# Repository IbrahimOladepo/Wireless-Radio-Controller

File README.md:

# Wireless Radio Controller
 A wireless radio controller DIY project based on NRF24L01 and Arduino

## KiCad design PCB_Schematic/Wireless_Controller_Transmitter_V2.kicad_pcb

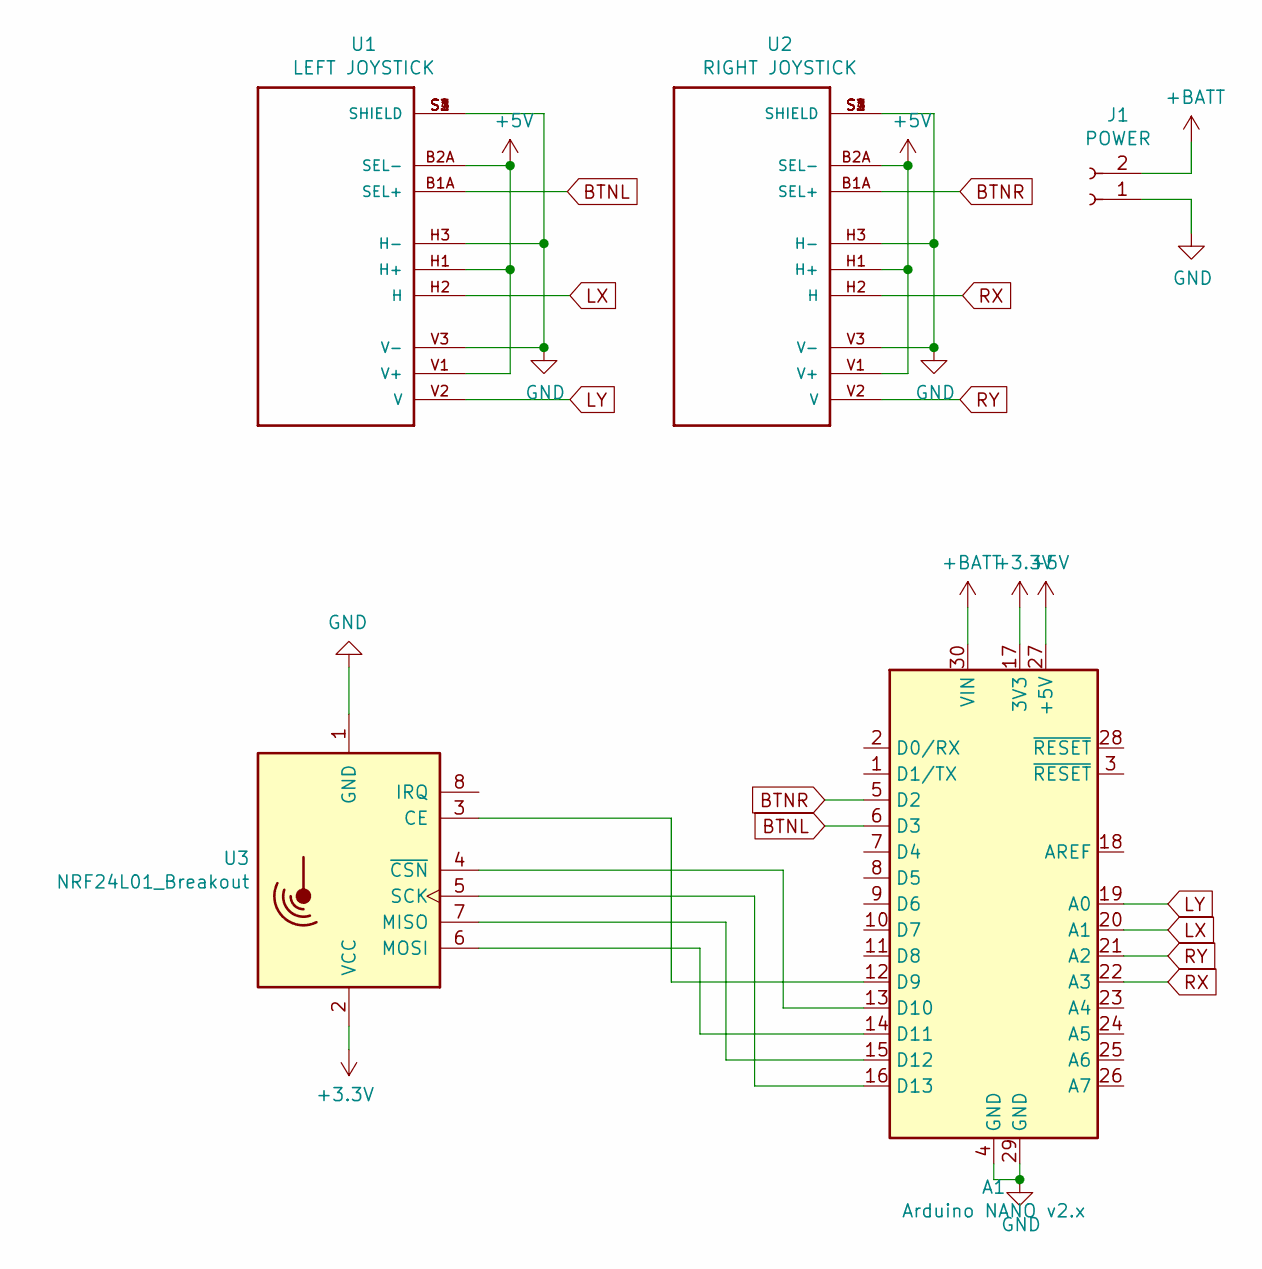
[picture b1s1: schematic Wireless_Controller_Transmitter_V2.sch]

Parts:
A1: Arduino NANO v2.x; Arduino_Nano
J1: POWER; PinHeader_1x02_P1.00mm_Vertical
U1: LEFT JOYSTICK; XDCR_COM-09032
U2: RIGHT JOYSTICK; XDCR_COM-09032
U3: NRF24L01_Breakout; nRF24L01_Breakout

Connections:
+3V3: A1.17 (3V3), U3.2 (VCC)
+5V: A1.27 (+5V), U1.B2A (SEL-), U1.H1 (H+), U1.V1 (V+), U2.B2A (SEL-), U2.H1 (H+), U2.V1 (V+)
+BATT: A1.30 (VIN), J1.2
BTNL: A1.6 (D3), U1.B1A (SEL+)
BTNR: A1.5 (D2), U2.B1A (SEL+)
GND: A1.4 (GND), A1.29 (GND), J1.1, U1.H3 (H-), U1.S1 (SHIELD), U1.S2 (SHIELD), U1.S3 (SHIELD), U1.S4 (SHIELD), U1.V3 (V-), U2.H3 (H-), U2.S1 (SHIELD), U2.S2 (SHIELD), U2.S3 (SHIELD), U2.S4 (SHIELD), U2.V3 (V-), U3.1 (GND)
LX: A1.20 (A1), U1.H2 (H)
LY: A1.19 (A0), U1.V2 (V)
unnamed: A1.12 (D9), U3.3 (CE)
unnamed: A1.13 (D10), U3.4 (~CSN)
unnamed: A1.14 (D11), U3.6 (MOSI)
unnamed: A1.15 (D12), U3.7 (MISO)
unnamed: A1.16 (D13), U3.5 (SCK)
RX: A1.22 (A3), U2.H2 (H)
RY: A1.21 (A2), U2.V2 (V)

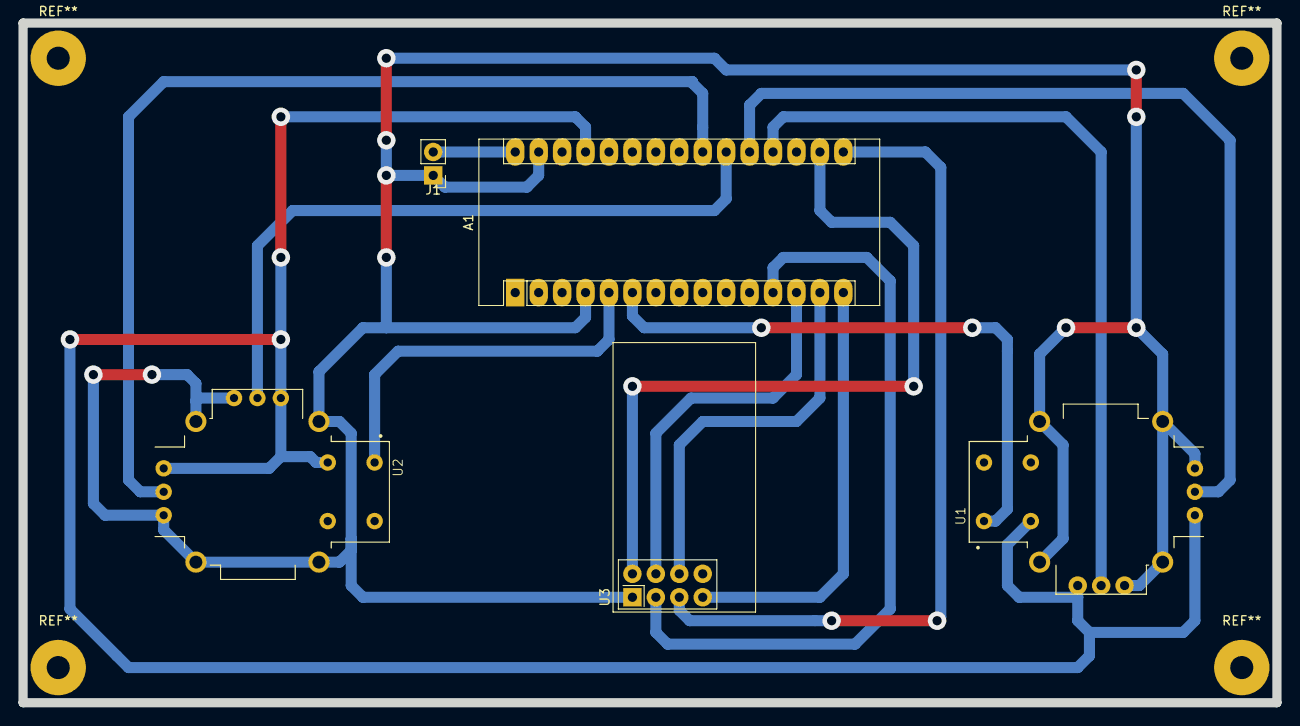
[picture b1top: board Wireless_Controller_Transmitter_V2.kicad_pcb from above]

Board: 2 copper layers, 135.9 x 73.7 mm, 5 parts (0 on the bottom side), 15 nets.

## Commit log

2020-08-18 Create configure
2020-08-18 Create Doxyfile
2020-08-18 Arduino NRF24L01 Library
